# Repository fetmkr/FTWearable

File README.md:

# FTWearable
Future Theater Wearable Device

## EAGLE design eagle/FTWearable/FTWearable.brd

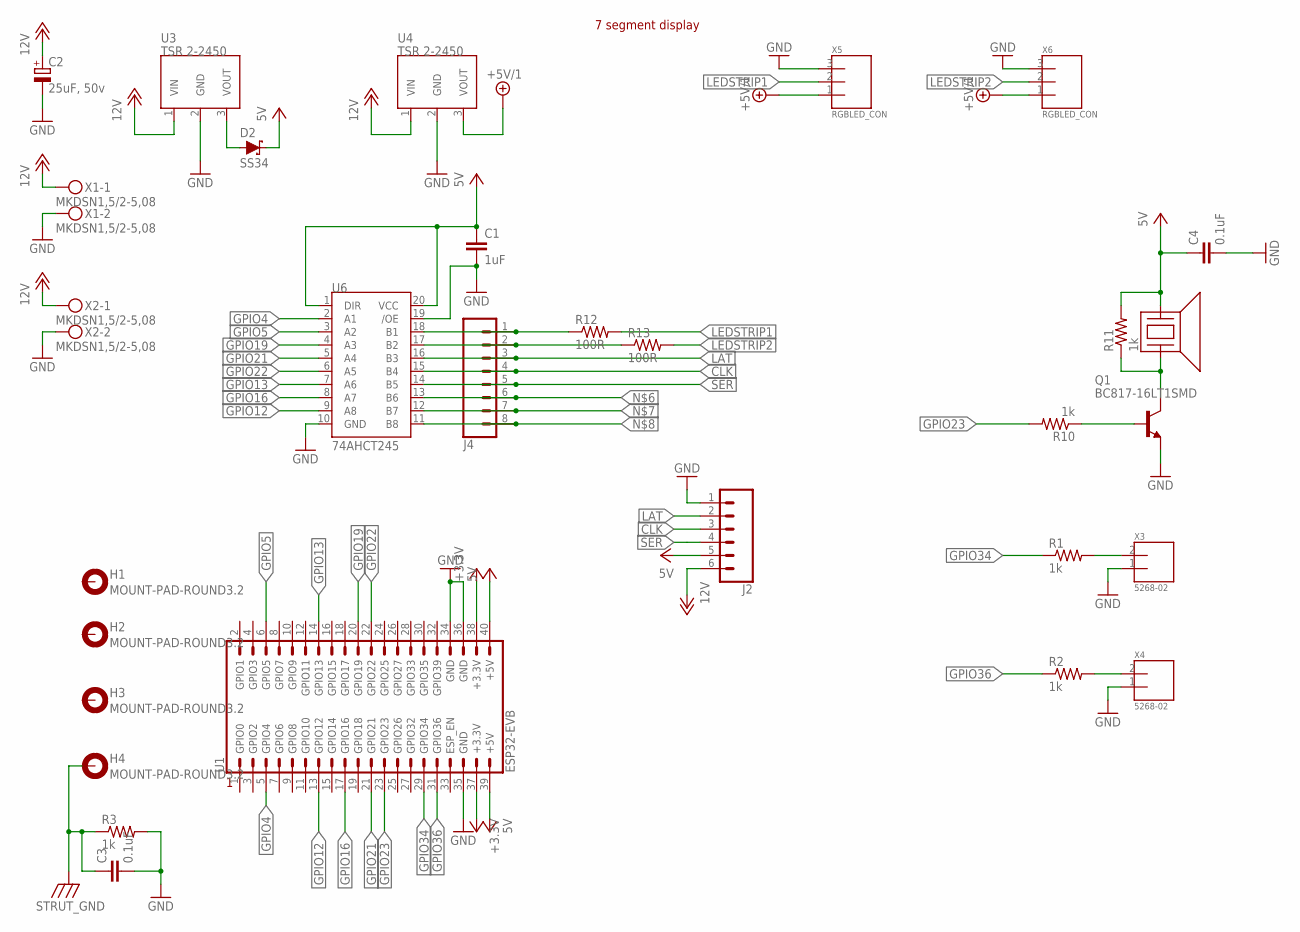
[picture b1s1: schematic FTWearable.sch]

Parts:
C1: 1uF; C0805(2012)_LEVEL_A
C2: 25uF, 50v; PANASONIC_B_LEVEL_A
C3, C4: 0.1uF; C0603(1608)_LEVEL_A
D2: SS34; DO-214BA
H1, H2, H3, H4: MOUNT-PAD-ROUND3.2; 3,2-PAD
J2: CONN_06SILK_FEMALE_PTH; 1X06
J4: CONN_08"; 1X08
LED1: SPARKFUN7SEGMENT
Q1: BC817-16LT1SMD; SOT23-BEC
R1, R2, R3, R10, R11: 1k; R0603(1608)_LEVEL_A
R12, R13: 100R; R0603(1608)_LEVEL_A
U1: ESP32-EVB
U3, U4: TSR 2-2450; TSR2
U5: BUZZER; PS1240
U6: 74AHCT245; TSSOP-20_LEVEL_A
X1, X2: MKDSN1,5/2-5,08
X3, X4: 5268-02; 5628-02
X5, X6: RGBLED_CON

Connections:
5V: C1.1, C4.1, D2.C, J2.5, R11.2, U1.39 (+5V), U1.40 (+5V), U5.1, U6.1 (DIR), U6.20 (VCC)
12V: C2.1 (+), J2.6, U3.1 (VIN), U4.1 (VIN), X1.1, X2.1
+3.3V: U1.37 (+3.3V), U1.38 (+3.3V)
+5V/1: U4.3 (VOUT), X5.1, X6.1
CLK: J2.3, J4.4, U6.15 (B4)
GND: C1.2, C2.2 (-), C3.2, C4.2, J2.1, Q1.E, R3.2, U1.34 (GND), U1.35 (GND), U1.36 (GND), U3.2 (GND), U4.2 (GND), U6.10 (GND), U6.19 (/OE), X1.2, X2.2, X3.1, X4.1, X5.3, X6.3
GPIO4: U1.5 (GPIO4), U6.2 (A1)
GPIO5: U1.6 (GPIO5), U6.3 (A2)
GPIO12: U1.13 (GPIO12), U6.9 (A8)
GPIO13: U1.14 (GPIO13), U6.7 (A6)
GPIO16: U1.17 (GPIO16), U6.8 (A7)
GPIO19: U1.20 (GPIO19), U6.4 (A3)
GPIO21: U1.21 (GPIO21), U6.5 (A4)
GPIO22: U1.22 (GPIO22), U6.6 (A5)
GPIO23: R10.2, U1.23 (GPIO23)
GPIO34: R1.1, U1.29 (GPIO34)
GPIO36: R2.1, U1.31 (GPIO36)
LAT: J2.2, J4.3, U6.16 (B3)
LEDSTRIP1: R12.2, X5.2
LEDSTRIP2: R13.2, X6.2
unnamed: R1.2, X3.2
unnamed: R2.2, X4.2
unnamed: J4.6, U6.13 (B6)
unnamed: J4.7, U6.12 (B7)
unnamed: J4.8, U6.11 (B8)
unnamed: J4.2, R13.1, U6.17 (B2)
unnamed: J4.1, R12.1, U6.18 (B1)
unnamed: Q1.B, R10.1
unnamed: Q1.C, R11.1, U5.2
unnamed: D2.A, U3.3 (VOUT)
SER: J2.4, J4.5, U6.14 (B5)
STRUT_GND: C3.1, H4.B3,2, R3.1

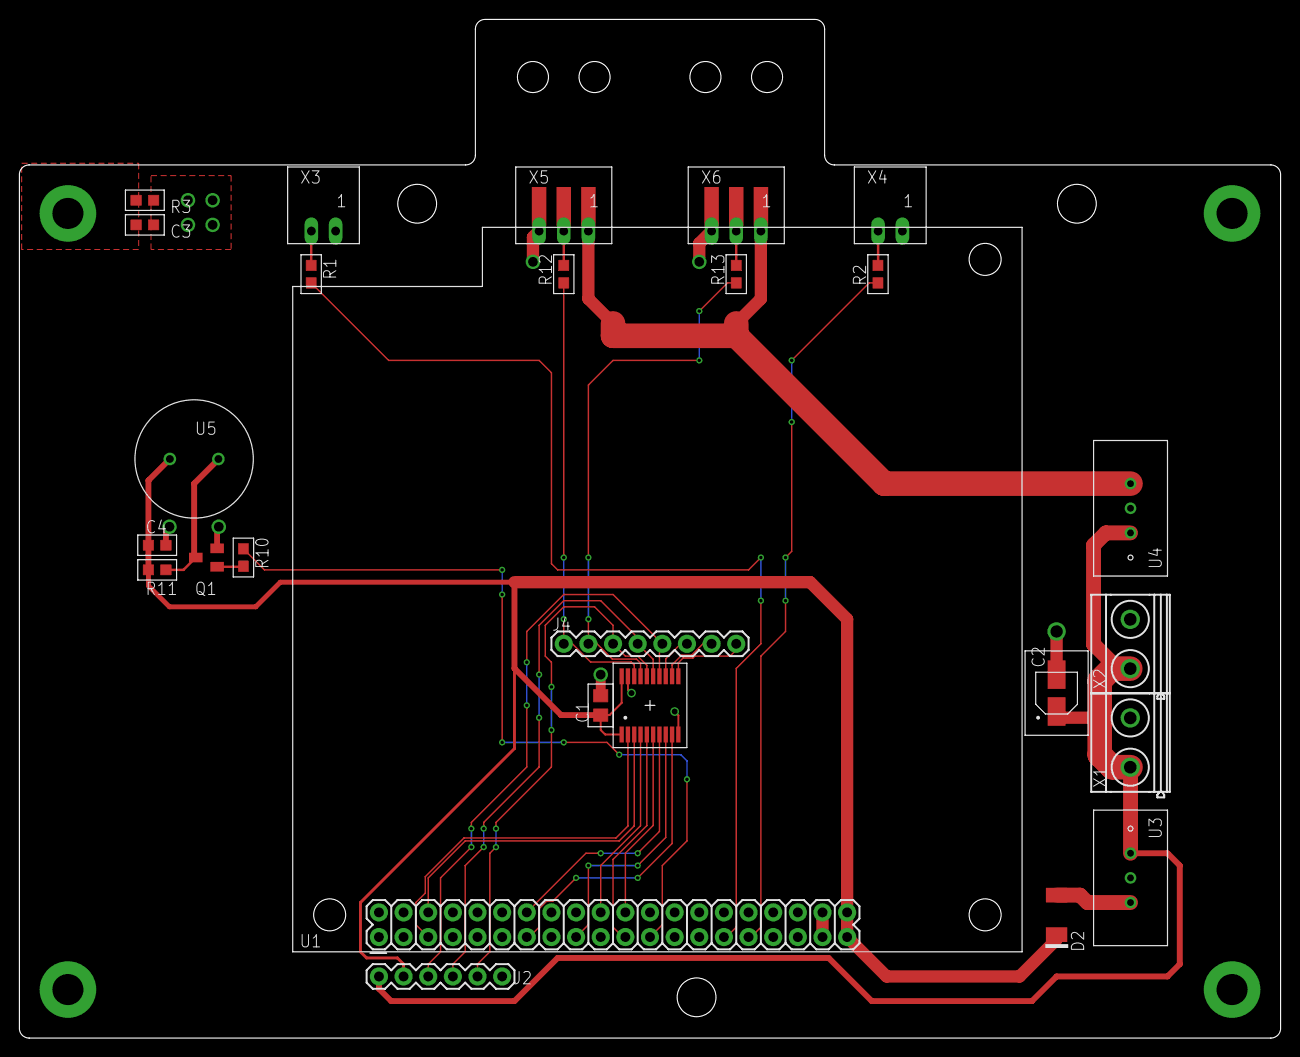
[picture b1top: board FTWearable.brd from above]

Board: 2 copper layers, 130.0 x 105.0 mm, 31 parts (1 on the bottom side), 32 nets.

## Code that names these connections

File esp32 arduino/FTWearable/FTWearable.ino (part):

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unsigned int flashState = LOW;              // LOW means led is *on*

// Output
// GPIO4 LEDStrip1
// GPIO5 LEDStrip2
// GPIO19 LAT
// GPIO21 CLK
// GPIO22 SER
// GPIO23 Buzzer
// GPIO32 Relay flash

// Input
// GPIO34 Button Left
// GPIO36 Button Right

int ledstrip1pin = 4;
int ledstrip2pin = 5;
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
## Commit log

2022-06-21 backup

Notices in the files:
parts and their libraries:
SparkFun-Connectors: Licensing: Creative Commons ShareAlike 4.0 International - https://creativecommons.org/licenses/by-sa/4.0
